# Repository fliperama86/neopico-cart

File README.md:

# neopico-cart

An open-source Neo Geo MVS/AES flash cartridge using SDRAM instead of expensive parallel SRAM, targeting ~$100 BOM vs ~$1500+ for existing solutions.

## Project Goals

- Support largest games (~96-128 MB total ROM)
- Fast load times (~4 seconds for largest games)
- Cost-effective design using SDRAM with bank interleaving (MiSTer-inspired)
- Open-source hardware and software

## Architecture

```
┌───────────────────────────────────────────────────────────┐
│                      Flash Cart PCB                       │
│                                                           │
│  ┌──────────┐      ┌─────────────┐      ┌─────────────┐  │
│  │ SD Card  │─SPI─▶│  RP2350B    │      │   128MB     │  │
│  │ (.ngfc)  │      │             │      │   SDRAM     │  │
│  └──────────┘      │ • SD/FAT32  │      └──────┬──────┘  │
│                    │ • Menu UI   │             │         │
│                    │ • Config    │         16-bit        │
│                    └──────┬──────┘             │         │
│                           │                    │         │
│                       PIO/QSPI                 │         │
│                      (20-30 MB/s)              │         │
│                           │                    │         │
│                           ▼                    ▼         │
│              ┌────────────────────────────────────────┐  │
│              │          FPGA (ECP5 or Gowin)          │  │
│              │  • SDRAM controller (120MHz)           │  │
│              │  • 4-bank interleaving                 │  │
│              │  • Neo Geo bus interface               │  │
│              │  • Menu video generation               │  │
│              └───────────────────┬────────────────────┘  │
│                                  │                       │
│                           Level Shifters                 │
│                                  │                       │
└──────────────────────────────────┼───────────────────────┘
                                   │ 5V Bus
                                   ▼
                         ┌───────────────────┐
                         │   Neo Geo MVS/AES │
                         │   Cartridge Slot  │
                         └───────────────────┘
```

### Why Two Chips?

**RP2350 (~$1.50)** handles "software" tasks that are easy in C but painful in HDL:
- SD card FAT32 filesystem parsing
- Menu system and user input
- Configuration and save management
- Uses PIO for high-speed FPGA data transfer (20-30 MB/s)

**FPGA** handles timing-critical tasks requiring nanosecond precision:
- SDRAM controller with 4-bank interleaving
- Neo Geo bus interface (<250ns response for C-ROM)
- Real-time data serving during gameplay

Microcontrollers cannot serve real-time bus data due to timing constraints. Only FPGA + fast memory can meet these requirements. MiSTer proves SDRAM works with proper data reorganization and bank interleaving.

### Boot Sequence

1. RP2350 boots, initializes FPGA (bitstream from flash)
2. RP2350 reads SD card, displays menu via FPGA video
3. User selects game
4. RP2350 streams .ngfc file to FPGA via PIO (~4 sec for largest games)
5. FPGA writes to SDRAM as data arrives
6. FPGA switches to "play" mode, serves all bus requests
7. RP2350 monitors for menu button combo

## Bill of Materials Estimate

| Component | Part | Est. Cost |
|-----------|------|-----------|
| FPGA | Gowin GW2A-18 or Lattice ECP5-25 | $20 |
| SDRAM | AS4C64M16D3 (128MB) | $10 |
| MCU | RP2350B | $2 |
| Flash | W25Q128 (16MB for menu/loader) | $2 |
| Level Shifters | TXB0108 or similar (×4) | $6 |
| SD Card Slot | micro-SD | $1 |
| Voltage Regulators | 3.3V, 1.2V | $2 |
| PCB | 4-layer, Neo Geo form factor | $15 |
| Passives & Connectors | | $10 |
| **Total** | | **~$70-80** |

With 30% margin for revisions: **~$100**

## Current Status

### Phase 1: Research & Tooling ✅ Complete

- [x] Analyze existing solutions (BackBit, MiSTer, NeoSD)
- [x] Document timing requirements
- [x] Extract MiSTer transformation algorithms
- [x] Create ROM converter tool
- [x] Define NGFC file format
- [x] Cost analysis

### Phase 2: FPGA Development (Next)

- [ ] Set up FPGA toolchain (Gowin or Lattice)
- [ ] Implement SDRAM controller with bank interleaving
- [ ] Benchmark SDRAM latency/bandwidth
- [ ] Implement Neo Geo bus sniffer (for timing analysis)

### Phase 3: Hardware Prototyping

- [ ] Design breakout board for FPGA dev kit → Neo Geo
- [ ] Measure real C-ROM timing on actual hardware
- [ ] Validate timing margins

### Phase 4+: Full Implementation, Testing, Release

## Tools

### NGFC Converter

The `ngfc/` directory contains a Python tool for converting standard Neo Geo ROM sets to the NGFC format, optimized for SDRAM burst access.

```bash
# Convert a MAME ROM set
./ngfc/ngfc_converter.py convert mslug.zip mslug.ngfc

# Verify an NGFC file
./ngfc/ngfc_converter.py verify mslug.ngfc
```

See [ngfc/README.md](ngfc/README.md) for full documentation.

## Documentation

- [Feasibility Study](docs/neogeo-flashcart-research.md) - Comprehensive technical analysis
- [NGFC Converter](ngfc/README.md) - ROM conversion tool documentation

## References

- [NeoGeo Development Wiki](https://wiki.neogeodev.org/)
- [MiSTer NeoGeo Core](https://github.com/MiSTer-devel/NeoGeo_MiSTer)
- [BackBit Platinum MVS](https://store.backbit.io/product/backbit-platinum-mvs/)

## License

See [LICENSE](LICENSE) for details.

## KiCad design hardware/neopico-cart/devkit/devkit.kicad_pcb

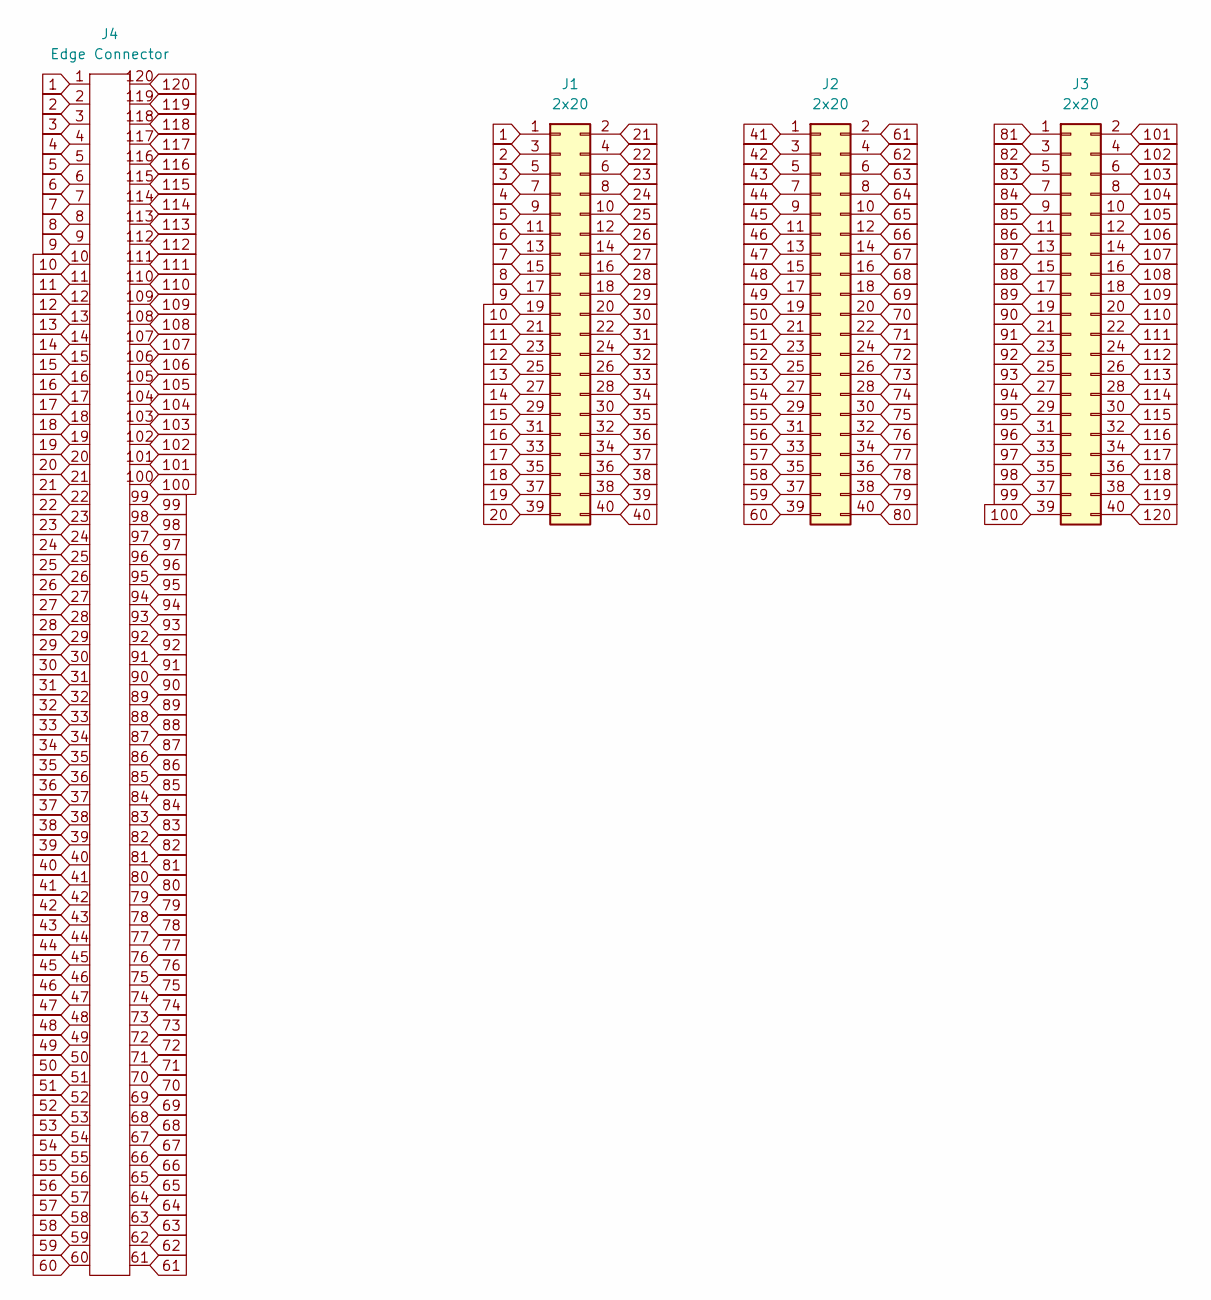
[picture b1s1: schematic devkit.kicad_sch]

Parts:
J1, J2, J3: 2x20; Samtec_HLE-120-02-xx-DV-TE_2x20_P2.54mm_Horizontal
J4: Edge Connector; NeoGeo_Cart_Edge_Connector

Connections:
1: J1.1, J4.1
2: J1.3, J4.2
3: J1.5, J4.3
4: J1.7, J4.4
5: J1.9, J4.5
6: J1.11, J4.6
7: J1.13, J4.7
8: J1.15, J4.8
9: J1.17, J4.9
10: J1.19, J4.10
11: J1.21, J4.11
12: J1.23, J4.12
13: J1.25, J4.13
14: J1.27, J4.14
15: J1.29, J4.15
16: J1.31, J4.16
17: J1.33, J4.17
18: J1.35, J4.18
19: J1.37, J4.19
20: J1.39, J4.20
21: J1.2, J4.21
22: J1.4, J4.22
23: J1.6, J4.23
24: J1.8, J4.24
25: J1.10, J4.25
26: J1.12, J4.26
27: J1.14, J4.27
28: J1.16, J4.28
29: J1.18, J4.29
30: J1.20, J4.30
31: J1.22, J4.31
32: J1.24, J4.32
33: J1.26, J4.33
34: J1.28, J4.34
35: J1.30, J4.35
36: J1.32, J4.36
37: J1.34, J4.37
38: J1.36, J4.38
39: J1.38, J4.39
40: J1.40, J4.40
41: J2.1, J4.41
42: J2.3, J4.42
43: J2.5, J4.43
44: J2.7, J4.44
45: J2.9, J4.45
46: J2.11, J4.46
47: J2.13, J4.47
48: J2.15, J4.48
49: J2.17, J4.49
50: J2.19, J4.50
51: J2.21, J4.51
52: J2.23, J4.52
53: J2.25, J4.53
54: J2.27, J4.54
55: J2.29, J4.55
56: J2.31, J4.56
57: J2.33, J4.57
58: J2.35, J4.58
59: J2.37, J4.59
60: J2.39, J4.60
61: J2.2, J4.61
62: J2.4, J4.62
63: J2.6, J4.63
64: J2.8, J4.64
65: J2.10, J4.65
66: J2.12, J4.66
67: J2.14, J4.67
68: J2.16, J4.68
69: J2.18, J4.69
70: J2.20, J4.70
71: J2.22, J4.71
72: J2.24, J4.72
73: J2.26, J4.73
74: J2.28, J4.74
75: J2.30, J4.75
76: J2.32, J4.76
77: J2.34, J4.77
78: J2.36, J4.78
79: J2.38, J4.79
80: J2.40, J4.80
81: J3.1, J4.81
82: J3.3, J4.82
83: J3.5, J4.83
84: J3.7, J4.84
85: J3.9, J4.85
86: J3.11, J4.86
87: J3.13, J4.87
88: J3.15, J4.88
89: J3.17, J4.89
90: J3.19, J4.90
91: J3.21, J4.91
92: J3.23, J4.92
93: J3.25, J4.93
94: J3.27, J4.94
95: J3.29, J4.95
96: J3.31, J4.96
97: J3.33, J4.97
98: J3.35, J4.98
99: J3.37, J4.99
100: J3.39, J4.100
101: J3.2, J4.101
102: J3.4, J4.102
103: J3.6, J4.103
104: J3.8, J4.104
105: J3.10, J4.105
106: J3.12, J4.106
107: J3.14, J4.107
108: J3.16, J4.108
109: J3.18, J4.109
110: J3.20, J4.110
111: J3.22, J4.111
112: J3.24, J4.112
113: J3.26, J4.113
114: J3.28, J4.114
115: J3.30, J4.115
116: J3.32, J4.116
117: J3.34, J4.117
118: J3.36, J4.118
119: J3.38, J4.119
120: J3.40, J4.120

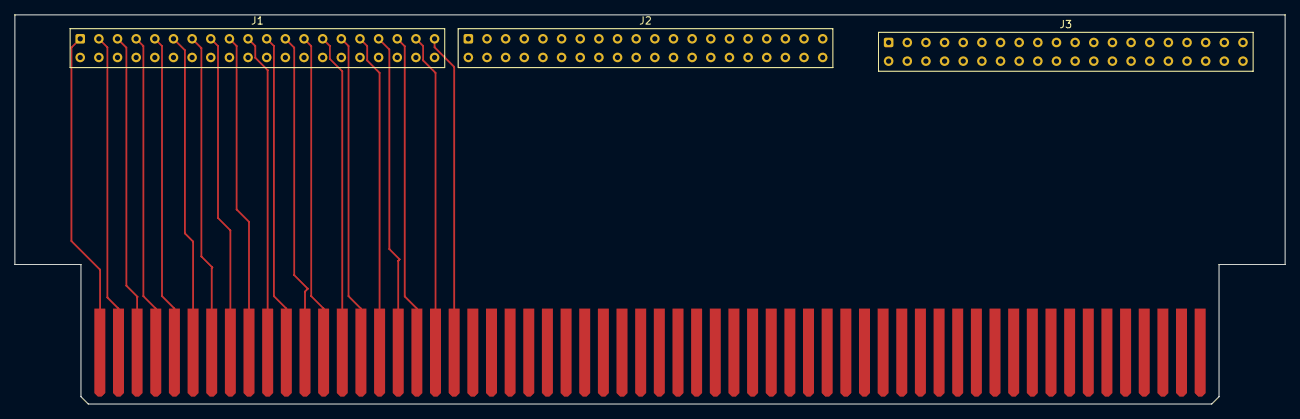
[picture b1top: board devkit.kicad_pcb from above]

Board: 2 copper layers, 173.0 x 53.0 mm, 4 parts (0 on the bottom side), 120 nets.

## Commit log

2025-12-14 Initial documentation
2025-12-14 Add readme file
2025-12-14 NGFC first version
2025-12-14 Add project stats
2025-12-14 Include Pico role in the docs
2025-12-24 update docs
2025-12-24 mooooore docs
2025-12-24 Fact-check Neo Geo MVS cartridge reference documentation
    Verified against NeoGeo Development Wiki and other reliable sources:
    - Corrected clock generation attribution (NEO-D0 generates ÷2,÷4,÷8;
    LSPC2-A2 generates ÷3,÷6)
    - Fixed NEO-D0 description (calendar is D4990 chip, not NEO-D0)
    - Updated NEO-B1 description (palette RAM is external SRAM)
    - Added uncertainty note to S-ROM timing requirement
2025-12-24 Fix ribbon cable claim and clarify C-ROM timing
    - Removed incorrect claim that boards are "connected via internal ribbon
    cables" - the CHA and PROG boards each have their own edge connector
    and plug into separate slots (CTRG1/CTRG2) on the motherboard
    - Clarified C-ROM timing: actual window is ~8 mclk (~333ns) per read,
    not 7 mclk as previously stated. The <250ns ROM requirement provides
    adequate margin within this window
2025-12-24 fix format
2025-12-24 Signal naming
2025-12-30 Update docs and hardware project
2025-12-30 Mem BOM
